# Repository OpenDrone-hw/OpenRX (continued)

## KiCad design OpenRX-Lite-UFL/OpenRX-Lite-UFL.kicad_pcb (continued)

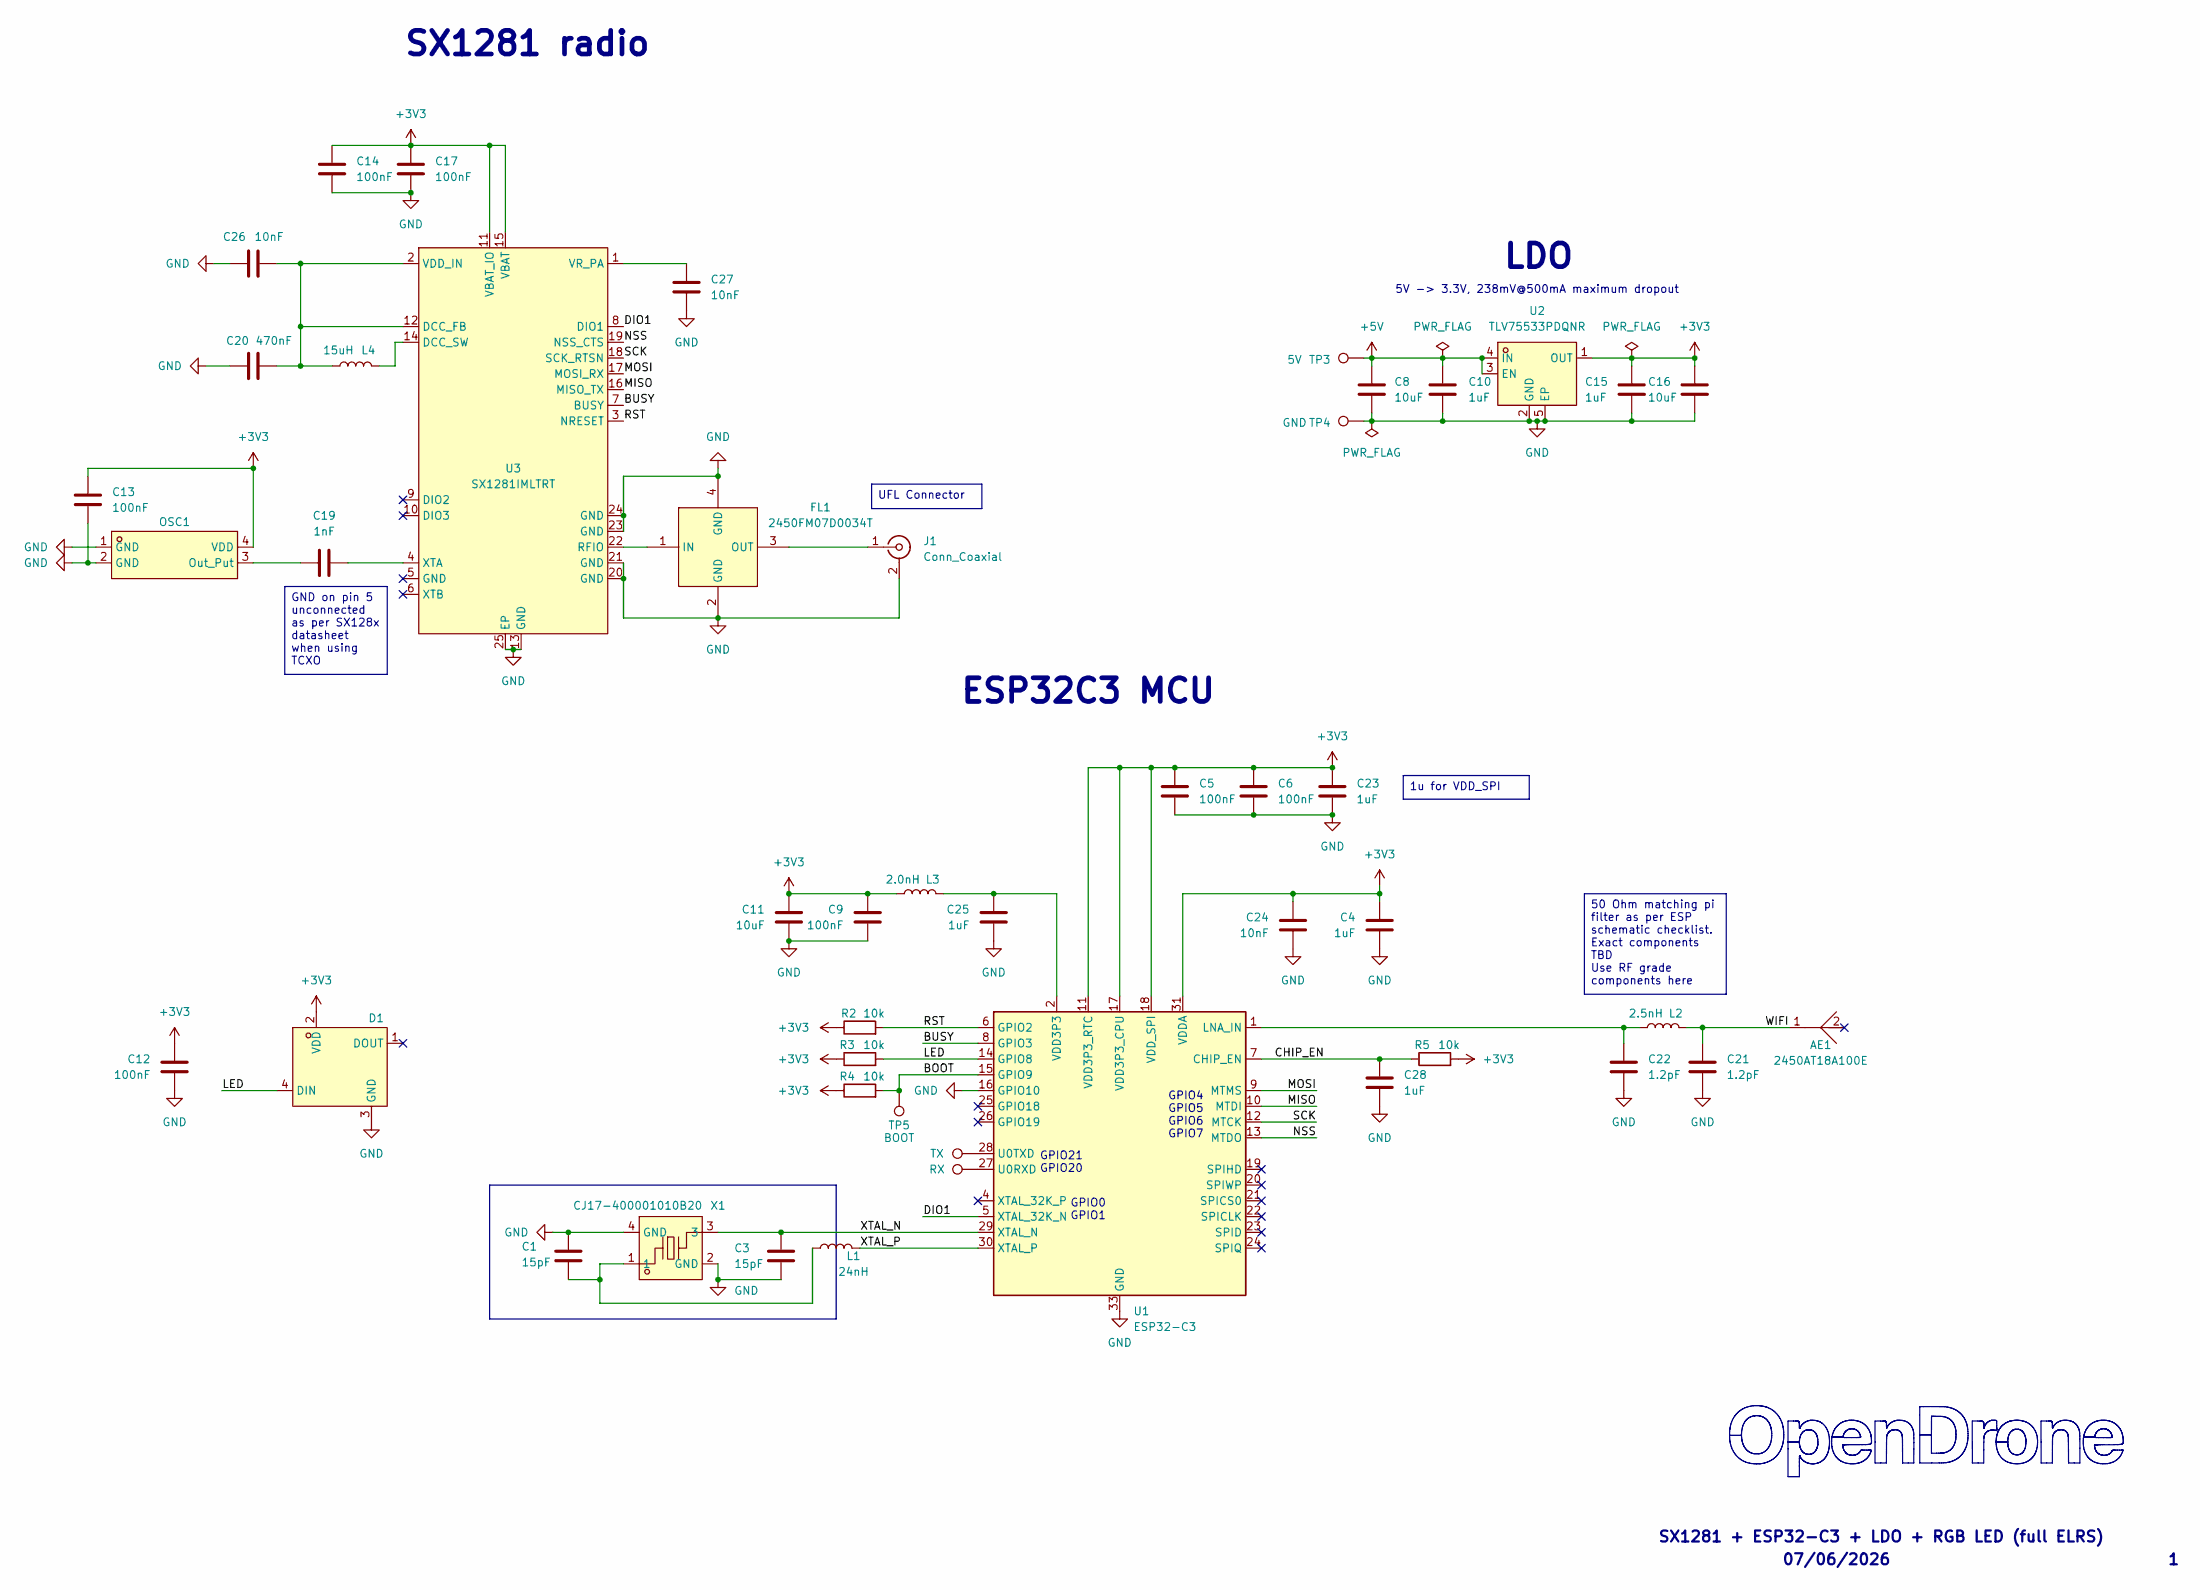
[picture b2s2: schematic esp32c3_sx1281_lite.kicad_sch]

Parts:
AE1: 2450AT18A100E; ANT-SMD_L3.2-W1.6; LCSC Part C89334
C1, C3: 15pF; C_0201_0603Metric; LCSC C85891
C4, C10, C15, C23, C25, C28: 1uF; C_0201_0603Metric; LCSC C76935
C5, C6, C9, C12, C13, C14, C17: 100nF; C_0201_0603Metric; LCSC C76939
C8, C16: 10uF; C_0402_1005Metric; LCSC C15525
C11: 10uF; C_0402_1005Metric; LCSC C76991
C19: 1nF; C_0201_0603Metric; LCSC C66942
C20: 470nF; C_0201_0603Metric; LCSC C85926
C21, C22: 1.2pF; C_0201_0603Metric; LCSC C85895
C24, C26, C27: 10nF; C_0201_0603Metric; LCSC C2168164
D1: XL-1010RGBC-WS2812B; LED-SMD_4P-L1.0-W1.0-TL_XL-1010RGBC-WS2812B; LCSC Part C5349953
FL1: 2450FM07D0034T; FILTER-SMD_4P-L1.0-W0.5-L; MPN 2450FM07D0034T; LCSC Part C2651081
J1: Conn_Coaxial; U.FL_Hirose_U.FL-R-SMT-1_Vertical; LCSC C88374
L1: 24nH; L_0201_0603Metric; LCSC C206441
L2: 2.5nH; L_0201_0603Metric; LCSC C206435
L3: 2.0nH; L_0201_0603Metric; LCSC C86125
L4: 15uH; L_0805_2012Metric
OSC1: OW7EL89CENUNFAYLC-52M; OSC-SMD_4P-L2.0-W1.6-BL_TXC_7Z; LCSC Part C22434896
R2, R3, R4, R5: 10k; R_0201_0603Metric; LCSC C106225
TP1: RX; SolderPad_1.2x2.0mm
TP2: TX; SolderPad_1.2x2.0mm
TP3: 5V; SolderPad_1.2x2.0mm
TP4: GND; SolderPad_1.2x2.0mm
TP5: BOOT; SolderPad_1.2x2.0mm
U1: ESP32-C3; QFN-32-1EP_5x5mm_P0.5mm_EP3.7x3.7mm
U2: TLV75533PDQNR; X2SON-4_L1.0-W1.0-P0.65-TL-EP; LCSC Part C2861882
U3: SX1281IMLTRT; QFN-24_L4.0-W4.0-P0.50-TL-EP2.6; LCSC Part C2151551
X1: CJ17-400001010B20; CRYSTAL-SMD_4P-L1.6-W1.2-BL; LCSC Part C2875272

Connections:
+3V3: C4.1, C5.1, C6.1, C9.1, C11.1, C12.1, C13.1, C14.1, C15.1, C16.1, C17.1, C23.1, C24.1, D1.2 (VDD), L3.2, OSC1.4 (VDD), R2.1, R3.1, R4.1, R5.2, U1.11 (VDD3P3_RTC), U1.17 (VDD3P3_CPU), U1.18 (VDD_SPI), U1.31 (VDDA), U1.32 (VDDA), U2.1 (OUT), U3.11 (VBAT_IO), U3.15 (VBAT)
+5V: C8.1, C10.1, TP3.1 (1_1), U2.3 (EN), U2.4 (IN)
/ESP32-C3 + SX1281 Core (UFL)/BOOT: R4.2, TP5.1 (1_1), U1.15 (GPIO9)
/ESP32-C3 + SX1281 Core (UFL)/BUSY: U1.8 (GPIO3), U3.7 (BUSY)
/ESP32-C3 + SX1281 Core (UFL)/CHIP_EN: C28.1, R5.1, U1.7 (CHIP_EN)
/ESP32-C3 + SX1281 Core (UFL)/DIO1: U1.5 (XTAL_32K_N), U3.8 (DIO1)
/ESP32-C3 + SX1281 Core (UFL)/LED: D1.4 (DIN), R3.2, U1.14 (GPIO8)
/ESP32-C3 + SX1281 Core (UFL)/MISO: U1.10 (MTDI), U3.16 (MISO_TX)
/ESP32-C3 + SX1281 Core (UFL)/MOSI: U1.9 (MTMS), U3.17 (MOSI_RX)
/ESP32-C3 + SX1281 Core (UFL)/NSS: U1.13 (MTDO), U3.19 (NSS_CTS)
/ESP32-C3 + SX1281 Core (UFL)/RST: R2.2, U1.6 (GPIO2), U3.3 (NRESET)
/ESP32-C3 + SX1281 Core (UFL)/SCK: U1.12 (MTCK), U3.18 (SCK_RTSN)
/ESP32-C3 + SX1281 Core (UFL)/WIFI: AE1.1, C21.1, L2.1
/ESP32-C3 + SX1281 Core (UFL)/XTAL_N: C3.1, U1.29 (XTAL_N), X1.3
/ESP32-C3 + SX1281 Core (UFL)/XTAL_P: L1.2, U1.30 (XTAL_P)
GND: C1.2, C3.2, C4.2, C5.2, C6.2, C8.2, C9.2, C10.2, C11.2, C12.2, C13.2, C14.2, C15.2, C16.2, C17.2, C20.1, C21.2, C22.2, C23.2, C24.2, C25.2, C26.1, C27.2, C28.2, D1.3 (GND), FL1.2 (GND), FL1.4 (GND), J1.2 (Ext), OSC1.1 (GND), OSC1.2 (GND), TP4.1 (1_1), U1.16 (GPIO10), U1.33 (GND), U2.2 (GND), U2.5 (EP), U3.13 (GND), U3.20 (GND), U3.21 (GND), U3.23 (GND), U3.24 (GND), U3.25 (EP), X1.2 (GND), X1.4 (GND)
unnamed: C1.1, L1.1, X1.1
unnamed: C25.1, L3.1, U1.2 (VDD3P3), U1.3 (VDD3P3)
unnamed: FL1.1 (IN), U3.22 (RFIO)
unnamed: FL1.3 (OUT), J1.1 (In)
unnamed: C19.1, OSC1.3 (Out_Put)
unnamed: C22.1, L2.2, U1.1 (LNA_IN)
unnamed: TP1.1 (1_1), U1.27 (U0RXD)
unnamed: TP2.1 (1_1), U1.28 (U0TXD)
unnamed: C20.2, C26.2, L4.1, U3.2 (VDD_IN), U3.12 (DCC_FB)
unnamed: L4.2, U3.14 (DCC_SW)
unnamed: C27.1, U3.1 (VR_PA)
unnamed: C19.2, U3.4 (XTA)

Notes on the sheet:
5V -> 3.3V, 238mV@500mA maximum dropout
GPIO0 GPIO1
GPIO21 GPIO20
SX1281 + ESP32-C3 + LDO + RGB LED (full ELRS)
GPIO4 GPIO5 GPIO6 GPIO7
SX1281 radio
LDO
ESP32C3 MCU
07/06/2026
GND on pin 5 unconnected as per SX128x datasheet when using TCXO
UFL Connector
1u for VDD_SPI
50 Ohm matching pi filter as per ESP schematic checklist. Exact components TBD Use RF grade components here

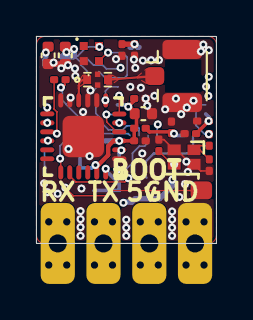
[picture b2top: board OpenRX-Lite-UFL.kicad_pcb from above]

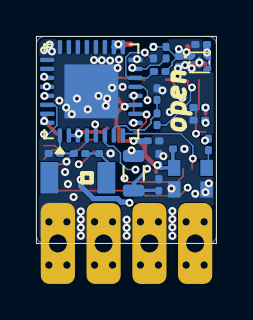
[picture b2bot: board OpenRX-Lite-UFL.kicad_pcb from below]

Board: 6 copper layers, 10.0 x 11.5 mm, 47 parts (22 on the bottom side), 28 nets.

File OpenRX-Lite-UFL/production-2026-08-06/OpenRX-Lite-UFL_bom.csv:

"Designator","Comment","Footprint","Qty","LCSC Part #"
"AE1","2450AT18A100E","OpenRX-Shared:ANT-SMD_L3.2-W1.6","1","C89334"
"C1,C3","15pF","Capacitor_SMD:C_0201_0603Metric","2","C85891"
"C4,C10,C15,C23,C25,C28","1uF","Capacitor_SMD:C_0201_0603Metric","6","C76935"
"C5,C6,C9,C12,C13,C14,C17","100nF","Capacitor_SMD:C_0201_0603Metric","7","C76939"
"C8,C16","10uF","Capacitor_SMD:C_0402_1005Metric","2","C15525"
"C11","10uF","Capacitor_SMD:C_0402_1005Metric","1","C76991"
"C19","1nF","Capacitor_SMD:C_0201_0603Metric","1","C66942"
"C20","470nF","Capacitor_SMD:C_0201_0603Metric","1","C85926"
"C21,C22","1.2pF","Capacitor_SMD:C_0201_0603Metric","2","C85895"
"C24,C26,C27","10nF","Capacitor_SMD:C_0201_0603Metric","3","C2168164"
"D1","XL-1010RGBC-WS2812B","OpenRX-Shared:LED-SMD_4P-L1.0-W1.0-TL_XL-1010RGBC-WS2812B","1",""
"FL1","2450FM07D0034T","OpenRX-Shared:FILTER-SMD_4P-L1.0-W0.5-L","1",""
"J1","Conn_Coaxial","Connector_Coaxial:U.FL_Hirose_U.FL-R-SMT-1_Vertical","1",""
"L1","24nH","Inductor_SMD:L_0201_0603Metric","1","C206441"
"L2","2.5nH","Inductor_SMD:L_0201_0603Metric","1","C206435"
"L3","2.0nH","Inductor_SMD:L_0201_0603Metric","1","C86125"
"L4","15uH","Inductor_SMD:L_0805_2012Metric","1",""
"OSC1","OW7EL89CENUNFAYLC-52M","OpenRX-Shared:OSC-SMD_4P-L2.0-W1.6-BL_TXC_7Z","1","C22434896"
"R2,R3,R4,R5","10k","Resistor_SMD:R_0201_0603Metric","4","C106225"
"TP1","RX","OpenRX-Shared:SolderPad_1.2x2.0mm","1",""
"TP2","TX","OpenRX-Shared:SolderPad_1.2x2.0mm","1",""
"TP3","5V","OpenRX-Shared:SolderPad_1.2x2.0mm","1",""
"TP4","GND","OpenRX-Shared:SolderPad_1.2x2.0mm","1",""
"TP5","BOOT","OpenRX-Shared:SolderPad_1.2x2.0mm","1",""
"U1","ESP32-C3","Package_DFN_QFN:QFN-32-1EP_5x5mm_P0.5mm_EP3.7x3.7mm","1",""
"U2","TLV75533PDQNR","OpenRX-Shared:X2SON-4_L1.0-W1.0-P0.65-TL-EP","1","C2861882"
"U3","SX1281IMLTRT","OpenRX-Shared:QFN-24_L4.0-W4.0-P0.50-TL-EP2.6","1","C2151551"
"X1","CJ17-400001010B20","OpenRX-Shared:CRYSTAL-SMD_4P-L1.6-W1.2-BL","1","C2875272"

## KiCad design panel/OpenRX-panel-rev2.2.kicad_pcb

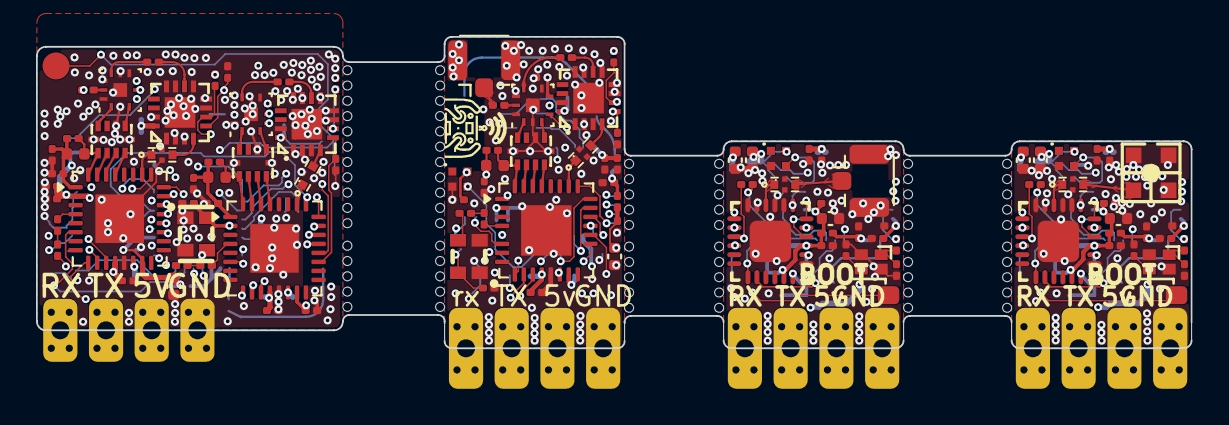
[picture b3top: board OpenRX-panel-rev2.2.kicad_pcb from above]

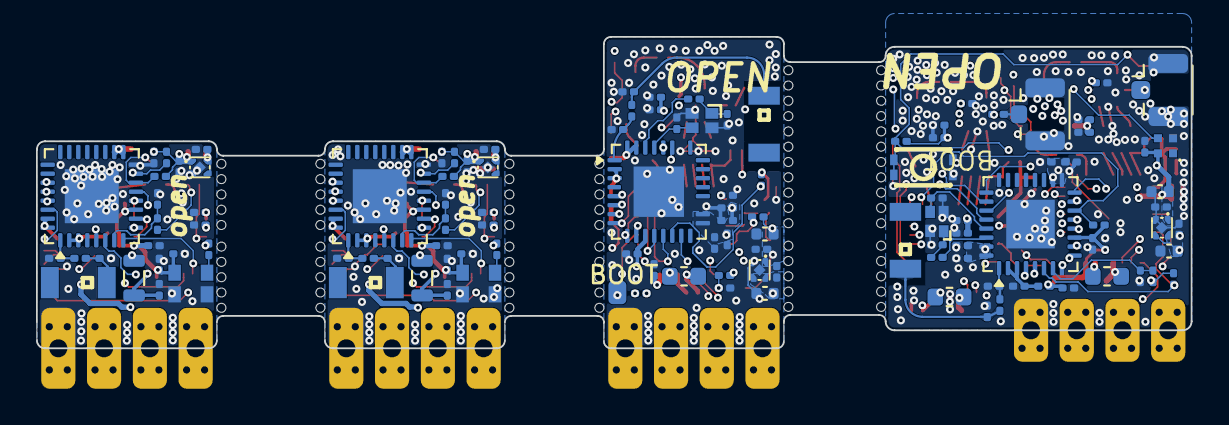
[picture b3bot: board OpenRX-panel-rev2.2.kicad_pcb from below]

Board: 6 copper layers, 64.2 x 17.3 mm, 241 parts (118 on the bottom side), 167 nets.

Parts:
AE1, AE101, AE201, AE301: 2450AT18A100E; ANT-SMD_L3.2-W1.6
AE302: 47948-0001; ANT-SMD_47948-0001
C1, C3, C101, C103, C201, C203, C301, C303: 15pF; C_0201_0603Metric
C2, C23, C24, C39, C42, C44, C102, C123, C124: 47p; C_0201_0603Metric
C4, C10, C17, C25, C27, C28, C31, C41, C104, C110, C117, C125, C127, C128, C131, C204, C210, C215, C223, C225, C228, C304, C310, C315, C323, C325, C328: 1uF; C_0201_0603Metric
C5, C6, C9, C12, C13, C14, C16, C35, C37, C105, C106, C109, C112, C113, C114, C116, C205, C206, C209, C212, C213, C214, C217, C305, C306, C309, C312, C313, C314, C317: 100nF; C_0201_0603Metric
C7, C34, C107: 10pF; C_0201_0603Metric
C8, C11, C18, C108, C111, C118, C208, C211, C216, C308, C311, C316: 10uF; C_0402_1005Metric
C15, C36, C115: 47pF; C_0201_0603Metric
C19, C33, C119: 2.2nF; C_0201_0603Metric
C20, C38, C120, C220, C320: 470nF; C_0201_0603Metric
C21, C40, C121: 220pF; C_0201_0603Metric
C22, C43, C122: 1n; C_0201_0603Metric
C26, C126, C224, C226, C227, C324, C326, C327: 10nF; C_0201_0603Metric
C29, C30, C129, C130, C221, C222, C321, C322: 1.2pF; C_0201_0603Metric
C219, C319: 1nF; C_0201_0603Metric
D1, D101, D201, D301: XL-1010RGBC-WS2812B; LED-SMD_4P-L1.0-W1.0-TL_XL-1010RGBC-WS2812B
FL1, FL2, FL101, FL201, FL301: 2450FM07D0034T; FILTER-SMD_4P-L1.0-W0.5-L
J1, J2, J101: Conn_Coaxial_Small; U.FL_Hirose_U.FL-R-SMT-1_Vertical
J201: Conn_Coaxial; U.FL_Hirose_U.FL-R-SMT-1_Vertical
L1, L6, L101: 10uH; L_0603_1608Metric
L2, L102, L201, L301: 24nH; L_0201_0603Metric
L3, L103, L203, L303: 2.0nH; L_0201_0603Metric
L4, L104, L202, L302: 2.5nH; L_0201_0603Metric
L5, L7, L105: 47nH; L_0402_1005Metric
L204, L304: 15uH; L_0805_2012Metric
OSC1, OSC101: OW7EL89CENUYO3YLC-32M; OSC-SMD_4P-L2.0-W1.6-BL_TXC_7Z
OSC201, OSC301: OW7EL89CENUNFAYLC-52M; OSC-SMD_4P-L2.0-W1.6-BL_TXC_7Z
R1, R10, R101: 200; R_0201_0603Metric
R2, R3, R4, R5, R102, R103, R104, R105, R202, R203, R204, R205, R302, R303, R304, R305: 10k; R_0201_0603Metric
R6, R9, R106: 220; R_0201_0603Metric
R7, R8, R11, R12, R107, R108: 100k; R_0201_0603Metric
T1, T2, T101: 0900PC16J0042001E; FILTER-SMD_10P-L2.0-W1.6-BL
TP1, TP101, TP201, TP301: RX; SolderPad_1.2x2.0mm
TP2, TP102, TP202, TP302: TX; SolderPad_1.2x2.0mm
TP3, TP103, TP203, TP303: 5V; SolderPad_1.2x2.0mm
TP4, TP104, TP204, TP304: GND; SolderPad_1.2x2.0mm
TP5: TestPoint; TestPoint_Pad_D1.5mm
TP105, TP205, TP305: BOOT; SolderPad_1.2x2.0mm
U1, U101, U201, U301: ESP32-C3; QFN-32-1EP_5x5mm_P0.5mm_EP3.7x3.7mm
U2, U102, U202, U302: TLV75533PDQNR; X2SON-4_L1.0-W1.0-P0.65-TL-EP
U3, U6, U103: LR1121IMLTRT; QFN-32-1EP_5x5mm_P0.5mm_EP3.7x3.7mm
U4, U7, U104: RFX2401C; QFN-16_L3.0-W3.0-P0.50-BL-EP1.7
U5, U8, U105: SKY13373-460LF; QFN-12_EP_2x2_Pitch0.5mm
U9: TS2306A 240GF MSM 9_C2976675; SW-SMD_4P-L3.0-W2.0-P0.85-LS3.5
U203, U303: SX1281IMLTRT; QFN-24_L4.0-W4.0-P0.50-TL-EP2.6
X1, X101, X201, X301: CJ17-400001010B20; CRYSTAL-SMD_4P-L1.6-W1.2-BL

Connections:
OpenRX-Gemini/+3V3: C4.1, C5.1, C6.1, C9.1, C11.1, C12.1, C13.2, C14.1, C15.1, C16.1, C17.1, C18.1, C21.1, C22.1, C26.1, C27.1, C31.1, C35.1, C36.1, C37.1, C40.1, C41.1, C43.1, D1.2 (VDD), L3.2, OSC1.4 (VDD), R2.1, R3.1, R4.1, R5.2, R8.1, R12.1, U1.11 (VDD3P3_RTC), U1.17 (VDD3P3_CPU), U1.18 (VDD_SPI), U1.31 (VDDA), U1.32 (VDDA), U2.1 (OUT), U3.2 (VBAT_RF), U3.15 (VBAT), U4.16 (VDD), U5.6 (VDD), U6.2 (VBAT_RF), U6.15 (VBAT), U7.16 (VDD), U8.6 (VDD)
OpenRX-Gemini/+5V: C8.1, C10.1, TP3.1 (1_1), U2.3 (EN), U2.4 (IN)
OpenRX-Gemini//Clock/TCXO_Out: C7.2, C34.2, OSC1.3 (OutPut)
OpenRX-Gemini//ESP32-C3/BOOT: R4.2, TP5.1 (1_1), U1.15 (GPIO9), U9.1
OpenRX-Gemini//ESP32-C3/BUSY_A: U1.8 (GPIO3), U3.25 (DIO0/BUSY)
OpenRX-Gemini//ESP32-C3/BUSY_B: R3.2, U1.14 (GPIO8), U6.25 (DIO0/BUSY)
OpenRX-Gemini//ESP32-C3/CHIP_EN: C28.1, R5.1, U1.7 (CHIP_EN)
OpenRX-Gemini//ESP32-C3/DIO1_A: U1.5 (XTAL_32K_N), U3.9 (DIO9)
OpenRX-Gemini//ESP32-C3/DIO1_B: U1.25 (GPIO18), U6.9 (DIO9)
OpenRX-Gemini//ESP32-C3/LED: D1.4 (DIN), U1.26 (GPIO19)
OpenRX-Gemini//ESP32-C3/MISO: U1.10 (MTDI), U3.21 (DIO4), U6.21 (DIO4)
OpenRX-Gemini//ESP32-C3/MOSI: U1.9 (MTMS), U3.22 (DIO3), U6.22 (DIO3)
OpenRX-Gemini//ESP32-C3/NSS_A: U1.4 (XTAL_32K_P), U3.24 (DIO1)
OpenRX-Gemini//ESP32-C3/NSS_B: U1.13 (MTDO), U6.24 (DIO1)
OpenRX-Gemini//ESP32-C3/RST_A: R2.2, U1.6 (GPIO2), U3.6 (NRESET)
OpenRX-Gemini//ESP32-C3/RST_B: U1.16 (GPIO10), U6.6 (NRESET)
OpenRX-Gemini//ESP32-C3/SCK: U1.12 (MTCK), U3.23 (DIO2), U6.23 (DIO2)
OpenRX-Gemini//ESP32-C3/WIFI: AE1.1, C30.1, L4.1
OpenRX-Gemini//ESP32-C3/XTAL_N: C3.1, U1.29 (XTAL_N), X1.3
OpenRX-Gemini//ESP32-C3/XTAL_P: L2.2, U1.30 (XTAL_P)
OpenRX-Gemini//LR1121_A/CTRL1: U3.11 (DIO7), U5.4 (V1)
OpenRX-Gemini//LR1121_A/CTRL2: U3.10 (DIO8), U5.5 (V2)
OpenRX-Gemini//LR1121_A/RXEN24: R8.2, U3.20 (DIO5), U4.6 (RXEN)
OpenRX-Gemini//LR1121_A/TXEN24: R7.2, U3.19 (DIO6), U4.5 (TXEN)
OpenRX-Gemini//LR1121_A/VR_PA: C2.1, C19.1, L5.1, R1.1, U3.1 (VR_PA)
OpenRX-Gemini//LR1121_B/CTRL1: U6.11 (DIO7), U8.4 (V1)
OpenRX-Gemini//LR1121_B/CTRL2: U6.10 (DIO8), U8.5 (V2)
OpenRX-Gemini//LR1121_B/RXEN24: R12.2, U6.20 (DIO5), U7.6 (RXEN)
OpenRX-Gemini//LR1121_B/TXEN24: R11.2, U6.19 (DIO6), U7.5 (TXEN)
OpenRX-Gemini//LR1121_B/VR_PA: C33.1, C39.1, L7.1, R10.1, U6.1 (VR_PA)
OpenRX-Gemini/GND: C1.2, C2.2, C3.2, C4.2, C5.2, C6.2, C8.2, C9.2, C10.2, C11.2, C12.2, C13.1, C14.2, C15.2, C16.2, C17.2, C18.2, C19.2, C20.1, C21.2, C22.2, C25.2, C26.2, C27.2, C28.2, C29.2, C30.2, C31.2, C33.2, C35.2, C36.2, C37.2, C38.1, C39.2, C40.2, C41.2, C43.2, D1.3 (GND), FL1.2 (GND), FL1.4 (GND), FL2.2 (GND), FL2.4 (GND), J1.2 (Ext), J2.2 (Ext), OSC1.1 (GND), OSC1.2 (GND), R7.1, R11.1, T1.5 (GND), T1.7 (GND), T1.10 (GND), T2.5 (GND), T2.7 (GND), T2.10 (GND), TP4.1 (1_1), U1.33 (GND), U2.2 (GND), U2.5 (EP), U3.13 (GND), U3.33 (EP), U4.1 (GND), U4.2 (GND), U4.3 (GND), U4.7 (GND), U4.8 (GND), U4.9 (GND), U4.11 (GND), U4.12 (GND), U4.15 (GND), U4.17 (EP), U5.2 (GND), U5.7 (GND), U5.8 (GND), U5.10 (GND), U5.12 (GND), U5.13 (EP), U6.13 (GND), U6.33 (EP), U7.1 (GND), U7.2 (GND), U7.3 (GND), U7.7 (GND), U7.8 (GND), U7.9 (GND), U7.11 (GND), U7.12 (GND), U7.15 (GND), U7.17 (EP), U8.2 (GND), U8.7 (GND), U8.8 (GND), U8.10 (GND), U8.12 (GND), U8.13 (EP), U9.2, X1.2 (GND), X1.4 (GND)
OpenRX-Gemini/Net-(C1-Pad1): C1.1, L2.1, X1.1
OpenRX-Gemini/Net-(C7-Pad1): C7.1, R6.1
OpenRX-Gemini/Net-(C25-Pad1): C25.1, L3.1, U1.2 (VDD3P3), U1.3 (VDD3P3)
OpenRX-Gemini/Net-(C34-Pad1): C34.1, R9.1
OpenRX-Gemini/Net-(FL1-IN): FL1.1 (IN), U3.26 (RFIO_HF)
OpenRX-Gemini/Net-(FL1-OUT): FL1.3 (OUT), U4.4 (TXRX)
OpenRX-Gemini/Net-(FL2-IN): FL2.1 (IN), U6.26 (RFIO_HF)
OpenRX-Gemini/Net-(FL2-OUT): FL2.3 (OUT), U7.4 (TXRX)
OpenRX-Gemini/Net-(J1-In): C24.2, J1.1 (In)
OpenRX-Gemini/Net-(J2-In): C44.2, J2.1 (In)
OpenRX-Gemini/Net-(T1-RFI_N_LFO): T1.4 (RFI_N_LFO), U3.29 (RFI_N_LF0)
OpenRX-Gemini/Net-(T1-RFI_P_LFO): T1.3 (RFI_P_LFO), U3.30 (RFI_P_LF0)
OpenRX-Gemini/Net-(T1-RFO_HP_LF): L5.2, R1.2, T1.1 (RFO_HP_LF), U3.32 (RFO_HP_LF)
OpenRX-Gemini/Net-(T1-RFO_LP_LF): T1.2 (RFO_LP_LF), U3.31 (RFO_LP_LF)
OpenRX-Gemini/Net-(T1-RX): T1.6 (RX), U5.3 (J3)
OpenRX-Gemini/Net-(T1-TX_HP): T1.9 (TX_HP), U5.1 (J1)
OpenRX-Gemini/Net-(T2-RFI_N_LFO): T2.4 (RFI_N_LFO), U6.29 (RFI_N_LF0)
OpenRX-Gemini/Net-(T2-RFI_P_LFO): T2.3 (RFI_P_LFO), U6.30 (RFI_P_LF0)
OpenRX-Gemini/Net-(T2-RFO_HP_LF): L7.2, R10.2, T2.1 (RFO_HP_LF), U6.32 (RFO_HP_LF)
OpenRX-Gemini/Net-(T2-RFO_LP_LF): T2.2 (RFO_LP_LF), U6.31 (RFO_LP_LF)
OpenRX-Gemini/Net-(T2-RX): T2.6 (RX), U8.3 (J3)
OpenRX-Gemini/Net-(T2-TX_HP): T2.9 (TX_HP), U8.1 (J1)
OpenRX-Gemini/Net-(U1-LNA_IN): C29.1, L4.2, U1.1 (LNA_IN)
OpenRX-Gemini/Net-(U1-U0RXD): TP1.1 (1_1), U1.27 (U0RXD)
OpenRX-Gemini/Net-(U1-U0TXD): TP2.1 (1_1), U1.28 (U0TXD)
OpenRX-Gemini/Net-(U3-DCC_SW): L1.1, U3.14 (DCC_SW)
OpenRX-Gemini/Net-(U3-VREG): C20.2, L1.2, U3.12 (VREG)
OpenRX-Gemini/Net-(U3-XTA): R6.2, U3.4 (XTA)
OpenRX-Gemini/Net-(U4-ANT): C23.1, U4.10 (ANT)
OpenRX-Gemini/Net-(U5-J2): C23.2, U5.9 (J2)
OpenRX-Gemini/Net-(U5-RFC): C24.1, U5.11 (RFC)
OpenRX-Gemini/Net-(U6-DCC_SW): L6.1, U6.14 (DCC_SW)
OpenRX-Gemini/Net-(U6-VREG): C38.2, L6.2, U6.12 (VREG)
OpenRX-Gemini/Net-(U6-XTA): R9.2, U6.4 (XTA)
OpenRX-Gemini/Net-(U7-ANT): C42.1, U7.10 (ANT)
OpenRX-Gemini/Net-(U8-J2): C42.2, U8.9 (J2)
OpenRX-Gemini/Net-(U8-RFC): C44.1, U8.11 (RFC)
OpenRX-Lite-UFL/+3V3: C204.1, C205.1, C206.1, C209.1, C211.1, C212.1, C213.1, C214.1, C215.1, C216.1, C217.1, C223.1, C224.1, D201.2 (VDD), L203.2, OSC201.4 (VDD), R202.1, R203.1, R204.1, R205.2, U201.11 (VDD3P3_RTC), U201.17 (VDD3P3_CPU), U201.18 (VDD_SPI), U201.31 (VDDA), U201.32 (VDDA), U202.1 (OUT), U203.11 (VBAT_IO), U203.15 (VBAT)
OpenRX-Lite-UFL/+5V: C208.1, C210.1, TP203.1 (1_1), U202.3 (EN), U202.4 (IN)
OpenRX-Lite-UFL//ESP32-C3 + SX1281 Core (UFL)/BOOT: R204.2, TP205.1 (1_1), U201.15 (GPIO9)
OpenRX-Lite-UFL//ESP32-C3 + SX1281 Core (UFL)/BUSY: U201.8 (GPIO3), U203.7 (BUSY)
OpenRX-Lite-UFL//ESP32-C3 + SX1281 Core (UFL)/CHIP_EN: C228.1, R205.1, U201.7 (CHIP_EN)
OpenRX-Lite-UFL//ESP32-C3 + SX1281 Core (UFL)/DIO1: U201.5 (XTAL_32K_N), U203.8 (DIO1)
OpenRX-Lite-UFL//ESP32-C3 + SX1281 Core (UFL)/LED: D201.4 (DIN), R203.2, U201.14 (GPIO8)
OpenRX-Lite-UFL//ESP32-C3 + SX1281 Core (UFL)/MISO: U201.10 (MTDI), U203.16 (MISO_TX)
OpenRX-Lite-UFL//ESP32-C3 + SX1281 Core (UFL)/MOSI: U201.9 (MTMS), U203.17 (MOSI_RX)
OpenRX-Lite-UFL//ESP32-C3 + SX1281 Core (UFL)/NSS: U201.13 (MTDO), U203.19 (NSS_CTS)
OpenRX-Lite-UFL//ESP32-C3 + SX1281 Core (UFL)/RST: R202.2, U201.6 (GPIO2), U203.3 (NRESET)
OpenRX-Lite-UFL//ESP32-C3 + SX1281 Core (UFL)/SCK: U201.12 (MTCK), U203.18 (SCK_RTSN)
OpenRX-Lite-UFL//ESP32-C3 + SX1281 Core (UFL)/WIFI: AE201.1, C221.1, L202.1
OpenRX-Lite-UFL//ESP32-C3 + SX1281 Core (UFL)/XTAL_N: C203.1, U201.29 (XTAL_N), X201.3
OpenRX-Lite-UFL//ESP32-C3 + SX1281 Core (UFL)/XTAL_P: L201.2, U201.30 (XTAL_P)
OpenRX-Lite-UFL/GND: C201.2, C203.2, C204.2, C205.2, C206.2, C208.2, C209.2, C210.2, C211.2, C212.2, C213.2, C214.2, C215.2, C216.2, C217.2, C220.1, C221.2, C222.2, C223.2, C224.2, C225.2, C226.1, C227.2, C228.2, D201.3 (GND), FL201.2 (GND), FL201.4 (GND), J201.2 (Ext), OSC201.1 (GND), OSC201.2 (GND), TP204.1 (1_1), U201.16 (GPIO10), U201.33 (GND), U202.2 (GND), U202.5 (EP), U203.13 (GND), U203.20 (GND), U203.21 (GND), U203.23 (GND), U203.24 (GND), U203.25 (EP), X201.2 (GND), X201.4 (GND)
OpenRX-Lite-UFL/Net-(C1-Pad1): C201.1, L201.1, X201.1
OpenRX-Lite-UFL/Net-(C25-Pad1): C225.1, L203.1, U201.2 (VDD3P3), U201.3 (VDD3P3)
OpenRX-Lite-UFL/Net-(FL1-IN): FL201.1 (IN), U203.22 (RFIO)
OpenRX-Lite-UFL/Net-(FL1-OUT): FL201.3 (OUT), J201.1 (In)
OpenRX-Lite-UFL/Net-(OSC1-Out_Put): C219.1, OSC201.3 (Out_Put)
OpenRX-Lite-UFL/Net-(U1-LNA_IN): C222.1, L202.2, U201.1 (LNA_IN)
OpenRX-Lite-UFL/Net-(U1-U0RXD): TP201.1 (1_1), U201.27 (U0RXD)
OpenRX-Lite-UFL/Net-(U1-U0TXD): TP202.1 (1_1), U201.28 (U0TXD)
OpenRX-Lite-UFL/Net-(U3-DCC_FB): C220.2, C226.2, L204.1, U203.2 (VDD_IN), U203.12 (DCC_FB)
OpenRX-Lite-UFL/Net-(U3-DCC_SW): L204.2, U203.14 (DCC_SW)
OpenRX-Lite-UFL/Net-(U3-VR_PA): C227.1, U203.1 (VR_PA)
OpenRX-Lite-UFL/Net-(U3-XTA): C219.2, U203.4 (XTA)
OpenRX-Lite/+3V3: C304.1, C305.1, C306.1, C309.1, C311.1, C312.1, C313.1, C314.1, C315.1, C316.1, C317.1, C323.1, C324.1, D301.2 (VDD), L303.2, OSC301.4 (VDD), R302.1, R303.1, R304.1, R305.2, U301.11 (VDD3P3_RTC), U301.17 (VDD3P3_CPU), U301.18 (VDD_SPI), U301.31 (VDDA), U301.32 (VDDA), U302.1 (OUT), U303.11 (VBAT_IO), U303.15 (VBAT)
OpenRX-Lite/+5V: C308.1, C310.1, TP303.1 (1_1), U302.3 (EN), U302.4 (IN)
OpenRX-Lite//ESP32-C3 + SX1281 Core (UFL)/BOOT: R304.2, TP305.1 (1_1), U301.15 (GPIO9)
OpenRX-Lite//ESP32-C3 + SX1281 Core (UFL)/BUSY: U301.8 (GPIO3), U303.7 (BUSY)
OpenRX-Lite//ESP32-C3 + SX1281 Core (UFL)/CHIP_EN: C328.1, R305.1, U301.7 (CHIP_EN)
OpenRX-Lite//ESP32-C3 + SX1281 Core (UFL)/DIO1: U301.5 (XTAL_32K_N), U303.8 (DIO1)
OpenRX-Lite//ESP32-C3 + SX1281 Core (UFL)/LED: D301.4 (DIN), R303.2, U301.14 (GPIO8)
OpenRX-Lite//ESP32-C3 + SX1281 Core (UFL)/MISO: U301.10 (MTDI), U303.16 (MISO_TX)
OpenRX-Lite//ESP32-C3 + SX1281 Core (UFL)/MOSI: U301.9 (MTMS), U303.17 (MOSI_RX)
OpenRX-Lite//ESP32-C3 + SX1281 Core (UFL)/NSS: U301.13 (MTDO), U303.19 (NSS_CTS)
OpenRX-Lite//ESP32-C3 + SX1281 Core (UFL)/RST: R302.2, U301.6 (GPIO2), U303.3 (NRESET)
OpenRX-Lite//ESP32-C3 + SX1281 Core (UFL)/SCK: U301.12 (MTCK), U303.18 (SCK_RTSN)
OpenRX-Lite//ESP32-C3 + SX1281 Core (UFL)/WIFI: AE301.1, C321.1, L302.1
OpenRX-Lite//ESP32-C3 + SX1281 Core (UFL)/XTAL_N: C303.1, U301.29 (XTAL_N), X301.3
OpenRX-Lite//ESP32-C3 + SX1281 Core (UFL)/XTAL_P: L301.2, U301.30 (XTAL_P)
OpenRX-Lite/GND: AE302.1, AE302.2, AE302.4, C301.2, C303.2, C304.2, C305.2, C306.2, C308.2, C309.2, C310.2, C311.2, C312.2, C313.2, C314.2, C315.2, C316.2, C317.2, C320.1, C321.2, C322.2, C323.2, C324.2, C325.2, C326.1, C327.2, C328.2, D301.3 (GND), FL301.2 (GND), FL301.4 (GND), OSC301.1 (GND), OSC301.2 (GND), TP304.1 (1_1), U301.16 (GPIO10), U301.33 (GND), U302.2 (GND), U302.5 (EP), U303.13 (GND), U303.20 (GND), U303.21 (GND), U303.23 (GND), U303.24 (GND), U303.25 (EP), X301.2 (GND), X301.4 (GND)
OpenRX-Lite/Net-(C1-Pad1): C301.1, L301.1, X301.1
OpenRX-Lite/Net-(C25-Pad1): C325.1, L303.1, U301.2 (VDD3P3), U301.3 (VDD3P3)
OpenRX-Lite/Net-(FL1-IN): FL301.1 (IN), U303.22 (RFIO)
OpenRX-Lite/Net-(FL1-OUT): AE302.3, FL301.3 (OUT)
OpenRX-Lite/Net-(OSC1-Out_Put): C319.1, OSC301.3 (Out_Put)
OpenRX-Lite/Net-(U1-LNA_IN): C322.1, L302.2, U301.1 (LNA_IN)
OpenRX-Lite/Net-(U1-U0RXD): TP301.1 (1_1), U301.27 (U0RXD)
OpenRX-Lite/Net-(U1-U0TXD): TP302.1 (1_1), U301.28 (U0TXD)
OpenRX-Lite/Net-(U3-DCC_FB): C320.2, C326.2, L304.1, U303.2 (VDD_IN), U303.12 (DCC_FB)
OpenRX-Lite/Net-(U3-DCC_SW): L304.2, U303.14 (DCC_SW)
OpenRX-Lite/Net-(U3-VR_PA): C327.1, U303.1 (VR_PA)
OpenRX-Lite/Net-(U3-XTA): C319.2, U303.4 (XTA)
OpenRX-Mono/+3V3: C104.1, C105.1, C106.1, C109.1, C111.1, C112.1, C113.2, C114.1, C115.1, C116.1, C117.1, C118.1, C121.1, C122.1, C126.1, C127.1, C131.1, D101.2 (VDD), L103.2, OSC101.4 (VDD), R102.1, R103.1, R104.1, R105.2, R108.1, U101.11 (VDD3P3_RTC), U101.17 (VDD3P3_CPU), U101.18 (VDD_SPI), U101.31 (VDDA), U101.32 (VDDA), U102.1 (OUT), U103.2 (VBAT_RF), U103.15 (VBAT), U104.16 (VDD), U105.6 (VDD)
OpenRX-Mono/+5V: C108.1, C110.1, TP103.1 (1_1), U102.3 (EN), U102.4 (IN)
OpenRX-Mono//ESP32-C3 + LR1121 Mono/BOOT: R104.2, TP105.1 (1_1), U101.15 (GPIO9)
OpenRX-Mono//ESP32-C3 + LR1121 Mono/BUSY: U101.8 (GPIO3), U103.25 (DIO0/BUSY)
OpenRX-Mono//ESP32-C3 + LR1121 Mono/CHIP_EN: C128.1, R105.1, U101.7 (CHIP_EN)
OpenRX-Mono//ESP32-C3 + LR1121 Mono/CTRL1: U103.11 (DIO7), U105.4 (V1)
OpenRX-Mono//ESP32-C3 + LR1121 Mono/CTRL2: U103.10 (DIO8), U105.5 (V2)
OpenRX-Mono//ESP32-C3 + LR1121 Mono/DIO1: U101.5 (XTAL_32K_N), U103.9 (DIO9)
OpenRX-Mono//ESP32-C3 + LR1121 Mono/LED: D101.4 (DIN), R103.2, U101.14 (GPIO8)
OpenRX-Mono//ESP32-C3 + LR1121 Mono/MISO: U101.10 (MTDI), U103.21 (DIO4)
OpenRX-Mono//ESP32-C3 + LR1121 Mono/MOSI: U101.9 (MTMS), U103.22 (DIO3)
OpenRX-Mono//ESP32-C3 + LR1121 Mono/NSS: U101.13 (MTDO), U103.24 (DIO1)
OpenRX-Mono//ESP32-C3 + LR1121 Mono/RST: R102.2, U101.6 (GPIO2), U103.6 (NRESET)
OpenRX-Mono//ESP32-C3 + LR1121 Mono/RXEN24: R108.2, U103.20 (DIO5), U104.6 (RXEN)
OpenRX-Mono//ESP32-C3 + LR1121 Mono/SCK: U101.12 (MTCK), U103.23 (DIO2)
OpenRX-Mono//ESP32-C3 + LR1121 Mono/TXEN24: R107.2, U103.19 (DIO6), U104.5 (TXEN)
OpenRX-Mono//ESP32-C3 + LR1121 Mono/VR_PA: C102.1, C119.1, L105.1, R101.1, U103.1 (VR_PA)
OpenRX-Mono//ESP32-C3 + LR1121 Mono/WIFI: AE101.1, C130.1, L104.1
OpenRX-Mono//ESP32-C3 + LR1121 Mono/XTAL_N: C103.1, U101.29 (XTAL_N), X101.3
OpenRX-Mono//ESP32-C3 + LR1121 Mono/XTAL_P: L102.2, U101.30 (XTAL_P)
OpenRX-Mono/GND: C101.2, C102.2, C103.2, C104.2, C105.2, C106.2, C108.2, C109.2, C110.2, C111.2, C112.2, C113.1, C114.2, C115.2, C116.2, C117.2, C118.2, C119.2, C120.1, C121.2, C122.2, C125.2, C126.2, C127.2, C128.2, C129.2, C130.2, C131.2, D101.3 (GND), FL101.2 (GND), FL101.4 (GND), J101.2 (Ext), OSC101.1 (GND), OSC101.2 (GND), R107.1, T101.5 (GND), T101.7 (GND), T101.10 (GND), TP104.1 (1_1), U101.33 (GND), U102.2 (GND), U102.5 (EP), U103.13 (GND), U103.33 (EP), U104.1 (GND), U104.2 (GND), U104.3 (GND), U104.7 (GND), U104.8 (GND), U104.9 (GND), U104.11 (GND), U104.12 (GND), U104.15 (GND), U104.17 (EP), U105.2 (GND), U105.7 (GND), U105.8 (GND), U105.10 (GND), U105.12 (GND), U105.13 (EP), X101.2 (GND), X101.4 (GND)
OpenRX-Mono/Net-(C1-Pad1): C101.1, L102.1, X101.1
OpenRX-Mono/Net-(C7-Pad1): C107.1, R106.1
OpenRX-Mono/Net-(C25-Pad1): C125.1, L103.1, U101.2 (VDD3P3), U101.3 (VDD3P3)
OpenRX-Mono/Net-(FL1-IN): FL101.1 (IN), U103.26 (RFIO_HF)
OpenRX-Mono/Net-(FL1-OUT): FL101.3 (OUT), U104.4 (TXRX)
OpenRX-Mono/Net-(J1-In): C124.2, J101.1 (In)
OpenRX-Mono/Net-(OSC1-OutPut): C107.2, OSC101.3 (OutPut)
OpenRX-Mono/Net-(T1-RFI_N_LFO): T101.4 (RFI_N_LFO), U103.29 (RFI_N_LF0)
OpenRX-Mono/Net-(T1-RFI_P_LFO): T101.3 (RFI_P_LFO), U103.30 (RFI_P_LF0)
OpenRX-Mono/Net-(T1-RFO_HP_LF): L105.2, R101.2, T101.1 (RFO_HP_LF), U103.32 (RFO_HP_LF)
OpenRX-Mono/Net-(T1-RFO_LP_LF): T101.2 (RFO_LP_LF), U103.31 (RFO_LP_LF)
OpenRX-Mono/Net-(T1-RX): T101.6 (RX), U105.3 (J3)
OpenRX-Mono/Net-(T1-TX_HP): T101.9 (TX_HP), U105.1 (J1)
OpenRX-Mono/Net-(U1-LNA_IN): C129.1, L104.2, U101.1 (LNA_IN)
OpenRX-Mono/Net-(U1-U0RXD): TP101.1 (1_1), U101.27 (U0RXD)
OpenRX-Mono/Net-(U1-U0TXD): TP102.1 (1_1), U101.28 (U0TXD)
OpenRX-Mono/Net-(U3-DCC_SW): L101.1, U103.14 (DCC_SW)
OpenRX-Mono/Net-(U3-VREG): C120.2, L101.2, U103.12 (VREG)
OpenRX-Mono/Net-(U3-XTA): R106.2, U103.4 (XTA)
OpenRX-Mono/Net-(U4-ANT): C123.1, U104.10 (ANT)
OpenRX-Mono/Net-(U5-J2): C123.2, U105.9 (J2)
OpenRX-Mono/Net-(U5-RFC): C124.1, U105.11 (RFC)
